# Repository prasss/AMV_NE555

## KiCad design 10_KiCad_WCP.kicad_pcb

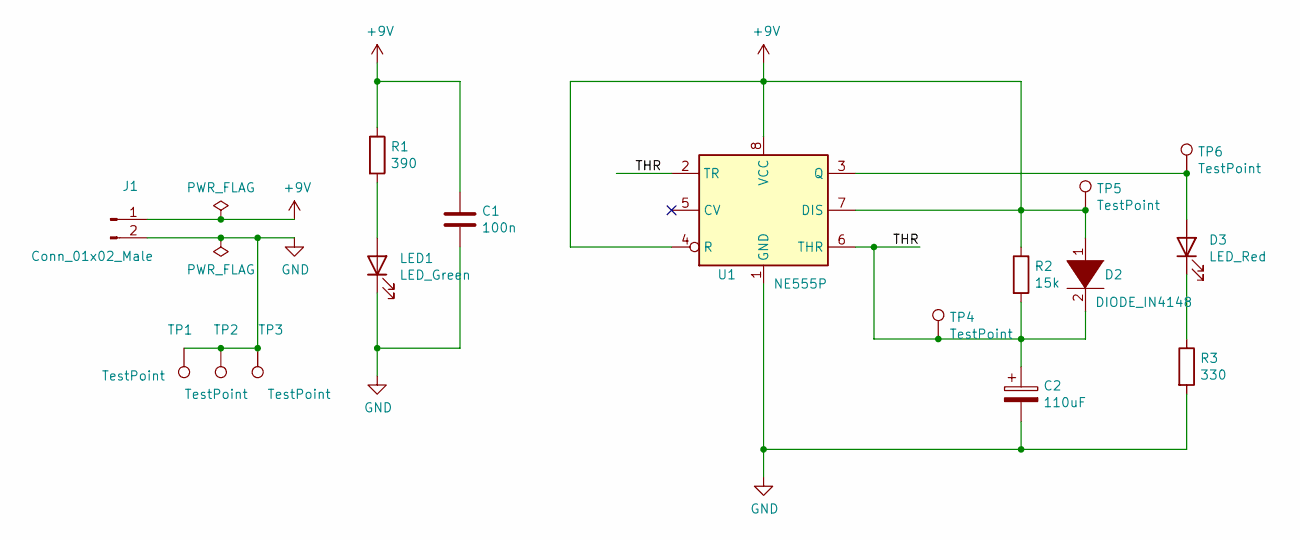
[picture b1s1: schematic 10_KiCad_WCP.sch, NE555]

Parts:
C1: 100n; C_Disc_D5.1mm_W3.2mm_P5.00mm
C2: 110uF; CP_Radial_D6.3mm_P2.50mm
D2: DIODE_IN4148; D_DO-35_SOD27_P7.62mm_Horizontal
D3: LED_Red; LED_D3.0mm
J1: Conn_01x02_Male; PinHeader_1x02_P2.54mm_Vertical
LED1: LED_Green; LED_1206_3216Metric_Pad1.42x1.75mm_HandSolder
R1: 390; R_1206_3216Metric_Pad1.30x1.75mm_HandSolder
R2: 15k; R_Axial_DIN0207_L6.3mm_D2.5mm_P7.62mm_Horizontal
R3: 330; R_Axial_DIN0207_L6.3mm_D2.5mm_P7.62mm_Horizontal
TP1, TP2, TP3, TP4, TP5, TP6: TestPoint; Pin_D1.0mm_L10.0mm
U1: NE555P; DIP-8_W7.62mm_Socket

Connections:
+9V: C1.1, D2.1 (K), J1.1, R1.1, R2.1, TP5.1, U1.4 (R), U1.7 (DIS), U1.8 (VCC)
/THR: C2.1, D2.2 (A), R2.2, TP4.1, U1.2 (TR), U1.6 (THR)
GND: C1.2, C2.2, J1.2, LED1.1 (K), R3.2, TP1.1, TP2.1, TP3.1, U1.1 (GND)
unnamed: D3.1 (K), R3.1
unnamed: D3.2 (A), TP6.1, U1.3 (Q)
unnamed: LED1.2 (A), R1.2

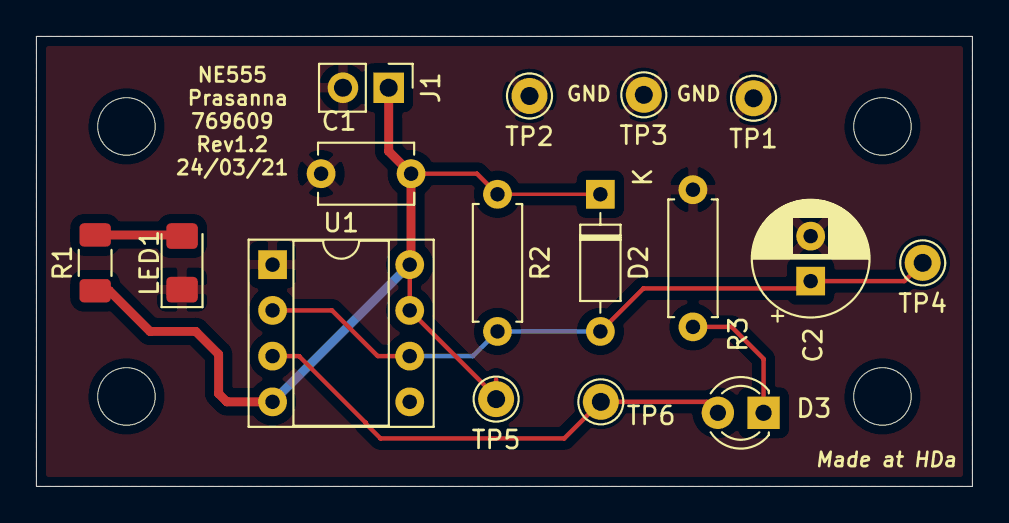
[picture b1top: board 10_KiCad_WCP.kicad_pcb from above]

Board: 2 copper layers, 52.0 x 25.0 mm, 16 parts (0 on the bottom side), 6 nets.

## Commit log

2021-04-02 Commit to Github
